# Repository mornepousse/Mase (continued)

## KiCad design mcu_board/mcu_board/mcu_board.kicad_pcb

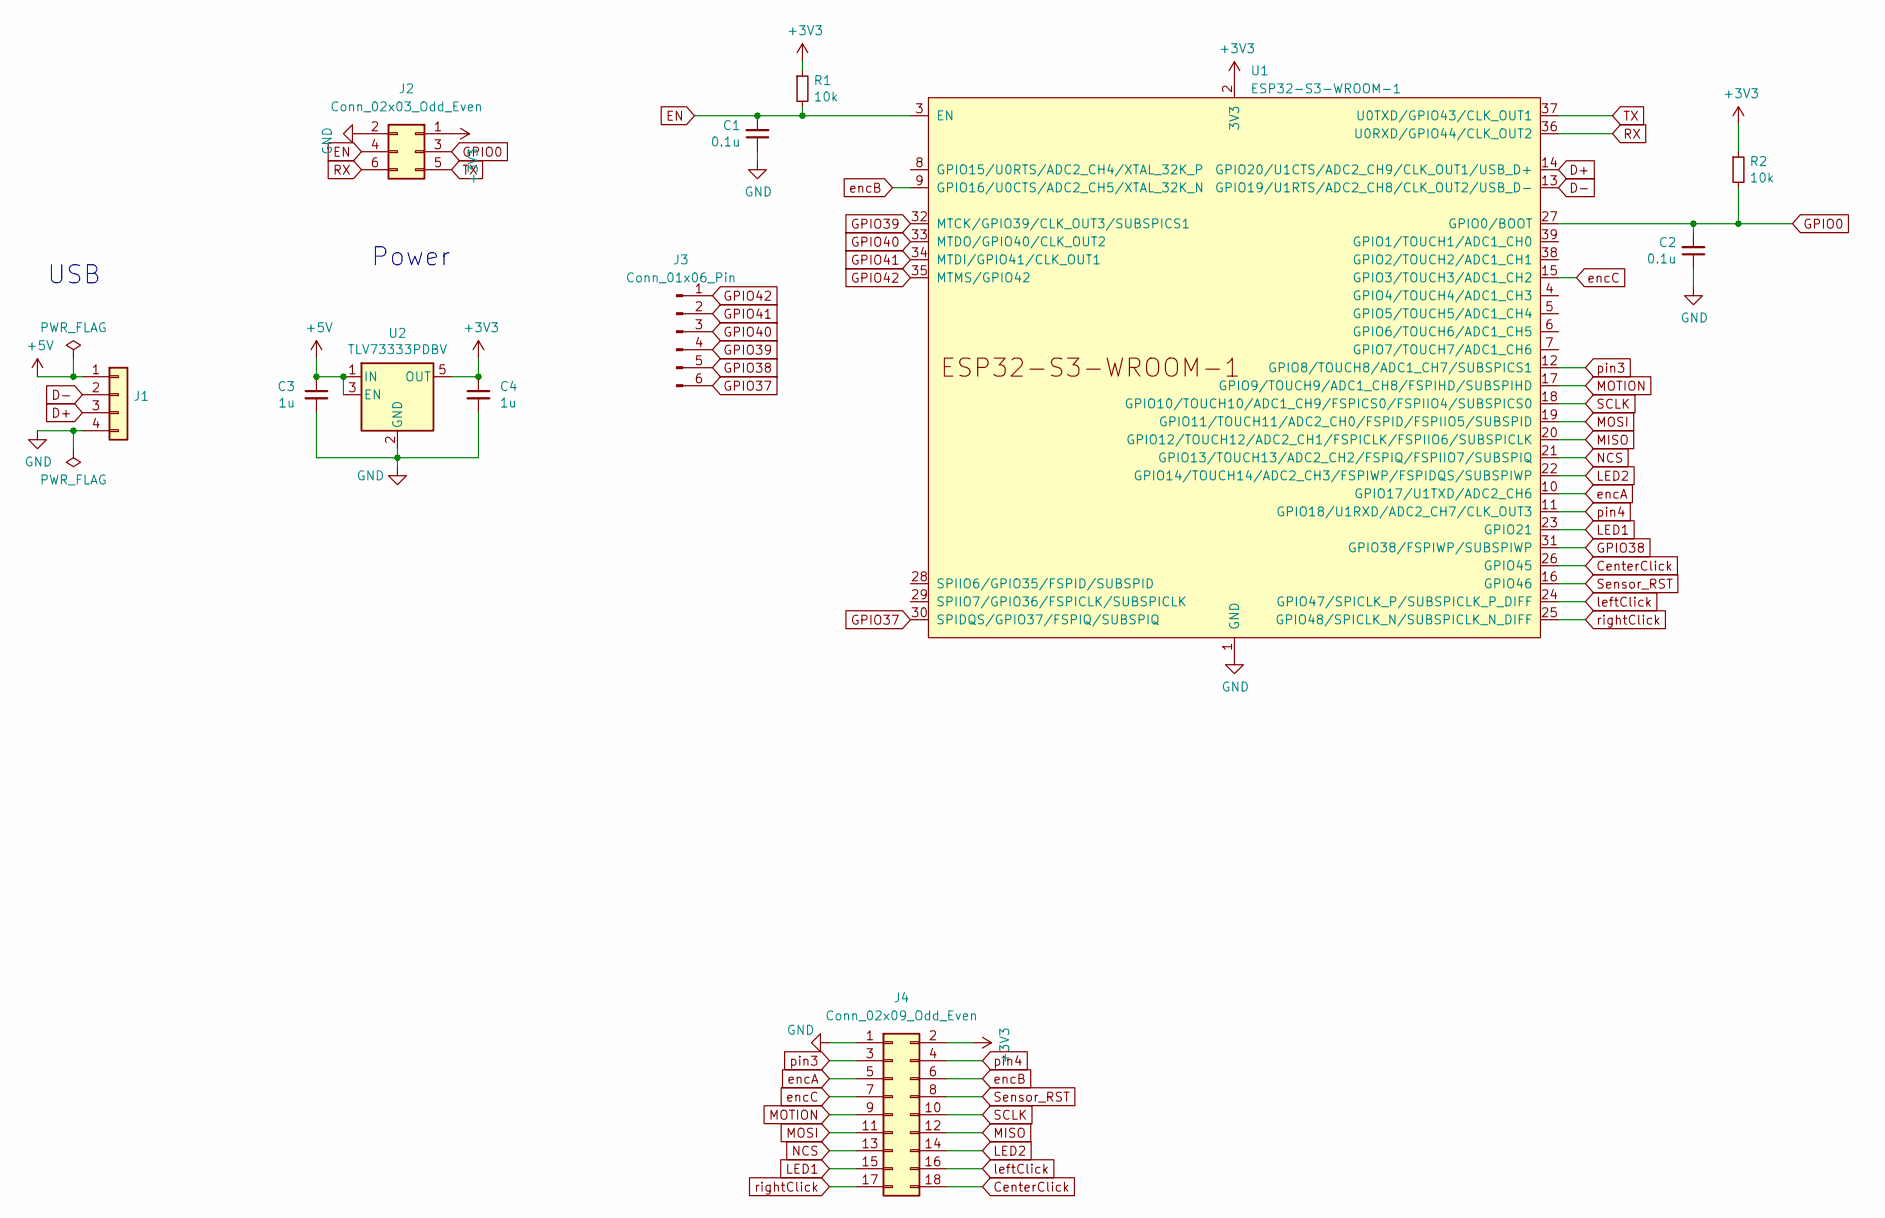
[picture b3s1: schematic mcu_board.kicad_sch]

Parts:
C1, C2: 0.1u; C_0805_2012Metric; LCSC C14663
C3, C4: 1u; C_0805_2012Metric; LCSC C52923
J1: Conn_01x04; PinHeader_1x04_P2.54mm_Vertical
J2: Conn_02x03_Odd_Even; Harwin_Gecko-G125-FVX0605L0X_2x03_P1.25mm_Vertical
J3: Conn_01x06_Pin; PinHeader_1x06_P2.00mm_Vertical
J4: Conn_02x09_Odd_Even; PinHeader_2x09_P2.54mm_Vertical
R1, R2: 10k; R_0805_2012Metric; LCSC C25744
U1: ESP32-S3-WROOM-1
U2: TLV73333PDBV; SOT-23-5; LCSC C134139

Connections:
+3V3: C4.1, J2.1, J4.2, R1.1, R2.1, U1.2 (3V3), U2.5 (OUT)
+5V: C3.1, J1.1, U2.1 (IN), U2.3 (EN)
CenterClick: J4.18, U1.26 (GPIO45)
D+: J1.3, U1.14 (GPIO20/U1CTS/ADC2_CH9/CLK_OUT1/USB_D+)
D-: J1.2, U1.13 (GPIO19/U1RTS/ADC2_CH8/CLK_OUT2/USB_D-)
EN: C1.2, J2.4, R1.2, U1.3 (EN)
GND: C1.1, C2.1, C3.2, C4.2, J1.4, J2.2, J4.1, U1.1 (GND), U1.40 (GND), U1.41 (GND), U2.2 (GND)
GPIO0: C2.2, J2.3, R2.2, U1.27 (GPIO0/BOOT)
GPIO37: J3.6, U1.30 (SPIDQS/GPIO37/FSPIQ/SUBSPIQ)
GPIO38: J3.5, U1.31 (GPIO38/FSPIWP/SUBSPIWP)
GPIO39: J3.4, U1.32 (MTCK/GPIO39/CLK_OUT3/SUBSPICS1)
GPIO40: J3.3, U1.33 (MTDO/GPIO40/CLK_OUT2)
GPIO41: J3.2, U1.34 (MTDI/GPIO41/CLK_OUT1)
GPIO42: J3.1, U1.35 (MTMS/GPIO42)
LED1: J4.15, U1.23 (GPIO21)
LED2: J4.14, U1.22 (GPIO14/TOUCH14/ADC2_CH3/FSPIWP/FSPIDQS/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)
MISO: J4.12, U1.20 (GPIO12/TOUCH12/ADC2_CH1/FSPICLK/FSPIIO6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)
MOSI: J4.11, U1.19 (GPIO11/TOUCH11/ADC2_CH0/FSPID/FSPIIO5/S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)
MOTION: J4.9, U1.17 (GPIO9/TOUCH9/ADC1_CH8/FSPIHD/SUBSPIHD)
NCS: J4.13, U1.21 (GPIO13/TOUCH13/ADC2_CH2/FSPIQ/FSPIIO7/S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)
RX: J2.6, U1.36 (U0RXD/GPIO44/CLK_OUT2)
SCLK: J4.10, U1.18 (GPIO10/TOUCH10/ADC1_CH9/FSPICS0/FSPIIO4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)
Sensor_RST: J4.8, U1.16 (GPIO46)
TX: J2.5, U1.37 (U0TXD/GPIO43/CLK_OUT1)
encA: J4.5, U1.10 (GPIO17/U1TXD/ADC2_CH6)
encB: J4.6, U1.9 (GPIO16/U0CTS/ADC2_CH5/XTAL_32K_N)
encC: J4.7, U1.15 (GPIO3/TOUCH3/ADC1_CH2)
leftClick: J4.16, U1.24 (GPIO47/SPICLK_P/SUBSPICLK_P_DIFF)
pin3: J4.3, U1.12 (GPIO8/TOUCH8/ADC1_CH7/SUBSPICS1)
pin4: J4.4, U1.11 (GPIO18/U1RXD/ADC2_CH7/CLK_OUT3)
rightClick: J4.17, U1.25 (GPIO48/SPICLK_N/SUBSPICLK_N_DIFF)

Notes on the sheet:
Power
USB

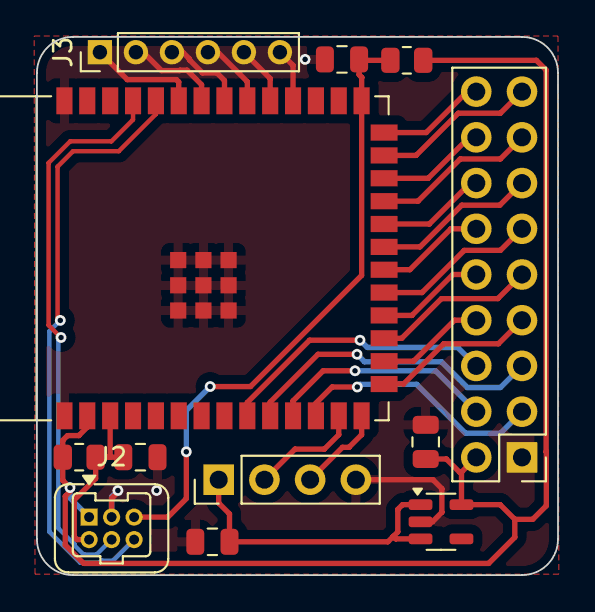
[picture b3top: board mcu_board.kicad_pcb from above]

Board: 2 copper layers, 28.9 x 29.9 mm, 12 parts (0 on the bottom side), 31 nets.

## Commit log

2025-01-10 First
2025-01-13 V1 prebuild
2025-01-13 changement wroom 2 a 1
2025-01-14 ajoute pin reset capteur optique
2025-01-14 ajoustement
2025-01-14 oups
2025-01-14 ajout test pad
2025-01-15 re-asignement des pins gpio
2025-01-15 update markdown
2025-01-16 changement empreinte bouton en\gpio0
2025-02-02 Passage a une molette standard et ajout circuit TP4056
2025-02-03 changement de taille
2025-02-11 repos
2025-02-11 next routing try
2025-02-12 add screen
2025-05-26 clean up for print test
2025-11-11 updatetest
2025-12-16 fist POC
2025-12-16 update3d
2025-12-16 update image
    Updated image reference in README.
2025-12-16 add readme
2025-12-16 3d ajustement
